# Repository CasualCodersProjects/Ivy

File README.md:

# Project Ivy
A chainable USB stepper driver system

# References for TMC2209 implementations
[fysetc](https://wiki.fysetc.com/Silent2209/#v31-hardware-connection)  
[Bigtreetech](https://github.com/bigtreetech/BIGTREETECH-TMC2209-V1.2/blob/master/Schematic/TMC2209-V1.2.pdf)

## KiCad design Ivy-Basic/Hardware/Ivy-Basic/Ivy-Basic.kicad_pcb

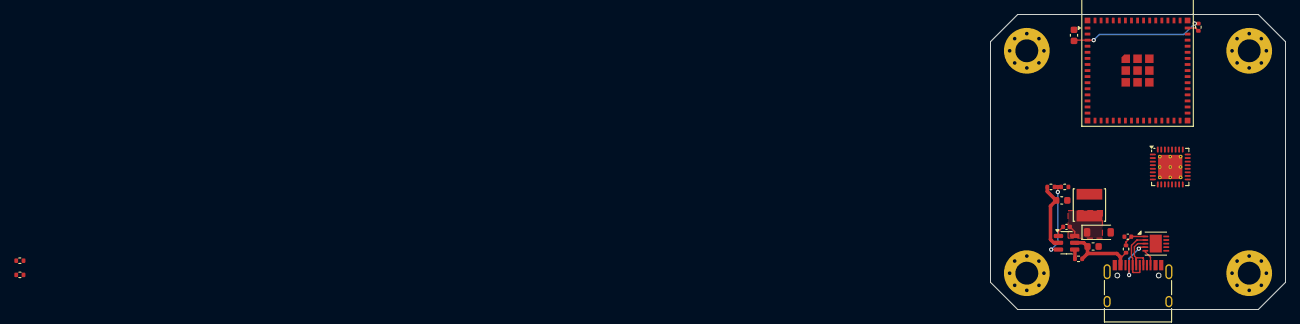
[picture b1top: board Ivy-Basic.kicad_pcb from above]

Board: 2 copper layers, 41.3 x 41.3 mm, 19 parts (0 on the bottom side), 24 nets.

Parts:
C1: 1u; C_0402_1005Metric
C2, C12: 10u; C_0603_1608Metric
C10: 100n; C_0402_1005Metric
C11: 4u7; C_0603_1608Metric
D1: D; D_SOD-123
IC1: SSP9451; SOT-23-6
J1: USB_C_Receptacle_USB2.0_16P; USB_C_Receptacle_HRO_TYPE-C-31-M-12
L1: 3u3; L_Abracon_ASPI-0425
R1: 10r; R_0402_1005Metric
R2, R3: 4k7; R_0402_1005Metric
R4: 10k; R_0402_1005Metric
R5: 124k; R_0402_1005Metric
R6: 40k2; R_0402_1005Metric
R10: 100k; R_0402_1005Metric
U1: ESP32-S3-MINI-1; ESP32-S2-MINI-1
U2: TMC2208-LA; TQFN-32-1EP_5x5mm_P0.5mm_EP3.4x3.4mm_ThermalVias
U3: DFN-10-1EP_3x3mm_P0.5mm_EP1.7x2.5mm

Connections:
+3V3: C2.1, C12.2, L1.2, R2.2, R3.2, R4.2, R5.2, U1.3 (3V3), U2.15 (VCC_IO)
/USB Power/CC1: J1.A5 (CC1), U3.4 (CC1)
/USB Power/CC2: J1.B5 (CC2), U3.5 (CC2)
CLK: U1.17 (IO13), U2.13 (CLK)
D+: J1.A7 (D-), J1.B7 (D-), U3.2 (D+)
D-: J1.A6 (D+), J1.B6 (D+), U3.3 (D-)
DIAG1: U1.11 (IO7), U2.11 (DIAG)
DIR1: U1.9 (IO5), U2.19 (DIR)
EN1: U1.14 (IO10), U2.2 (ENN)
FB: IC1.3 (FB), R5.1, R6.2
GND: C1.1, C2.2, C11.1, C12.1, D1.2 (A), IC1.2 (GND), J1.A1 (GND), J1.A12 (GND), J1.B1 (GND), J1.B12 (GND), J1.S1 (SHIELD), R6.1, U1.1 (GND), U1.2 (GND), U1.42 (GND), U1.43 (GND), U1.46 (GND), U1.47 (GND), U1.48 (GND), U1.49 (GND), U1.50 (GND), U1.51 (GND), U1.52 (GND), U1.53 (GND), U1.54 (GND), U1.55 (GND), U1.56 (GND), U1.57 (GND), U1.58 (GND), U1.59 (GND), U1.60 (GND), U1.61 (GND), U1.62 (GND), U1.63 (GND), U1.64 (GND), U1.65 (GND), U2.3 (GND), U2.18 (GND), U3.11 (GND)
INDEX1: U1.12 (IO8), U2.12 (INDEX)
MS1_1: U1.5 (IO1), U2.9 (MS1)
MS2_1: U1.6 (IO2), U2.10 (MS2)
unnamed: C10.2, D1.1 (K), IC1.6 (SW), L1.1
unnamed: C10.1, IC1.1 (CB)
unnamed: IC1.4 (EN), R10.1
unnamed: R4.1, U1.45 (EN)
unnamed: C1.2, R1.1, U3.1 (VIN)
SCL: R3.1, U3.7 (SCL)
SDA: R2.1, U3.6 (SDA)
STEP1: U1.8 (IO4), U2.16 (STEP)
UART: U1.16 (IO12), U2.14 (PDN_UART)
VBUS: C11.2, IC1.5 (VIN), J1.A4 (VBUS), J1.A9 (VBUS), J1.B4 (VBUS), J1.B9 (VBUS), R1.2, R10.2, U2.22 (VS), U2.28 (VS)

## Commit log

2024-10-24 Create Directories, add HUSB238 library
2024-10-24 Begin USB Power Sheet, ignore file locks, generate symbol library table
2024-10-25 USB PD Trigger Complete. Default to 20V.
2024-10-31 add switching buck converter
2024-11-01 add startup rc circuit to esp32
2024-11-08 I don't know what the diff is here
2024-11-09 ti switcher
2024-11-10 Replace buck converter with something that might work better
2024-11-10 Add 3D models, set board outline, place USB input, ESP32, Buck Converter
2024-11-24 add TMC2209
